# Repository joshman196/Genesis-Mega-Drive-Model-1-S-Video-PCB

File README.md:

# Sega Genesis/Mega Drive Model 1 S-Video Mod PCB
Simple PCB that carries the Luma, Chroma, and Ground lines with their respective components for a Model 1 Genesis/Mega Drive equipped with a Sony CXA1145 video encoder, enabling S-Video functionality. It is rare but still possible to instead have a Fujitsu MB3514 video encoder in a Model 1 Genesis/Mega Drive. If that is your case, then use the [Model 2 & 3 S-Video PCB instead](https://github.com/joshman196/Simple-Genesis-Model-2-and-3-S-Video-Private).

**It is recommended to use 28 AWG wire for this install.**

## Parts Needed

- 1x 220µF 6.3V Capacitor
- 1x 75 Ohm Resistor
- 1x 33 Ohm Resistor
- 1x KSC945 Transistor (If you buy this part from somewhere else, double-check that you get the KSC945 and **NOT** the KSC945**C**)

You can buy these components in a kit from [console5.com](https://console5.com/store/cxa1145-simple-s-video-mod-kit.html). Make sure to also pick up an S-Video jack as well, and conveniently enough console5 also offers these in either [socket](https://console5.com/store/mini-din-in-line-socket-4-pin-female-black-pin-type-s-video-s-vhs.html) or [panel mount](https://console5.com/store/s-video-jacks-panel-mount-black-plastic-housing-solder-type.html) configurations. The version you get depends on whether you want to drill the outer shell of your console (flush mount) or not (socket).

## Installation Steps

1. Add the components (capacitor, resistors, transistor) to the PCB and find a suitable place inside your console to put the assembled board at. You may want to put kapton tape on the area of the main board where you plan on setting the PCB at. Make sure your kapton tape layer can cover the entire bottom of the PCB. You may also choose to set it somewhere off of the main board.
2. Connect a wire from pin 15 of the CXA1145 to "C In" on the S-Video PCB.
3. Connect a wire from pin 16 of the CXA1145 to "Y In" on the S-Video PCB.
4. Connect a wire from pin 12 of the CXA1145 to "+5V In" on the S-Video PCB.
5. Connect a wire from pin 1 of the CXA1145 to "GND" on the S-Video PCB.
6. If you have heatshrink tubing that you want to use, you should prepare them on the next set of wires below before soldering the other ends of those wires. **Do not apply the heat to the tubing until after testing your install!**
7. Connect a wire from "C Out" on the S-Video PCB to the Chroma pin on the back of the S-Video jack.
8. Connect a wire from "Y Out" on the S-Video PCB to the Luma/Y pin on the back of the S-Video jack.
9. Connect a wire from "CGND" on the S-Video PCB to the Chroma-Ground pin on the back of the S-Video jack.
10. Connect a wire from "YGND" on the S-Video PCB to the Luma/Y-Ground pin on the back of the S-Video jack.
11. With the wiring all done, stick some more kapton tape from the sides over the PCB to stick it down onto the main board itself, setting the PCB on top of the other layer of kapton tape you put earlier. **DO NOT SET THE PCB DOWN ON THE BARE MAIN BOARD WITHOUT SOME KIND OF INSULATION UNDER THE S-VIDEO PCB TO PREVENT POTENTIAL SHORTS.** Electrical tape may work but that tends to leave a nasty residue, so I wouldn't recommend it.
12. You're done!

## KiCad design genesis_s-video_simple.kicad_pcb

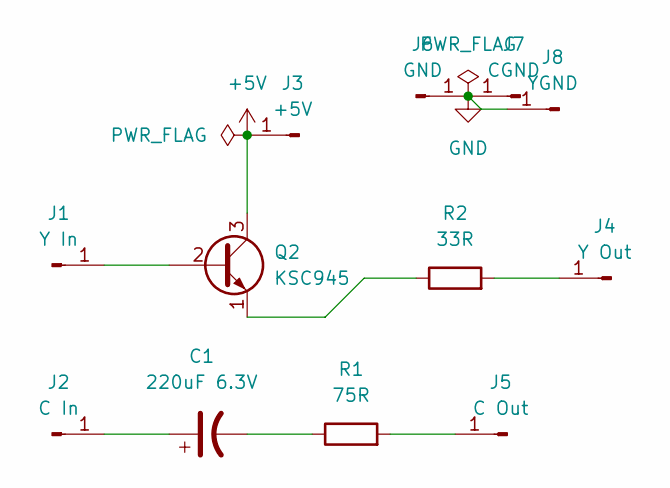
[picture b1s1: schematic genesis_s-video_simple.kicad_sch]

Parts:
C1: 220uF 6.3V; CP_Radial_D5.0mm_P2.50mm
J1: Y In; SolderWirePad_1x01_SMD_2x4mm
J2: C In; SolderWirePad_1x01_SMD_2x4mm
J3: +5V; SolderWirePad_1x01_SMD_2x4mm
J4: Y Out; SolderWirePad_1x01_SMD_2x4mm
J5: C Out; SolderWirePad_1x01_SMD_2x4mm
J6: GND; SolderWirePad_1x01_SMD_2x4mm
J7: CGND; SolderWirePad_1x01_SMD_2x4mm
J8: YGND; SolderWirePad_1x01_SMD_2x4mm
Q2: KSC945; TO-92L_Inline_Wide
R1: 75R; R_Axial_DIN0207_L6.3mm_D2.5mm_P10.16mm_Horizontal
R2: 33R; R_Axial_DIN0207_L6.3mm_D2.5mm_P10.16mm_Horizontal

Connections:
+5V: J3.1, Q2.3 (C); also elsewhere on the board
GND: J6.1, J7.1, J8.1
unnamed: C1.2, R1.1
unnamed 3: J1.1, Q2.2 (B); also elsewhere on the board
unnamed: C1.1, J2.1
unnamed: J4.1, R2.2
unnamed: J5.1, R1.2
unnamed 7: Q2.1 (E), R2.1; also elsewhere on the board

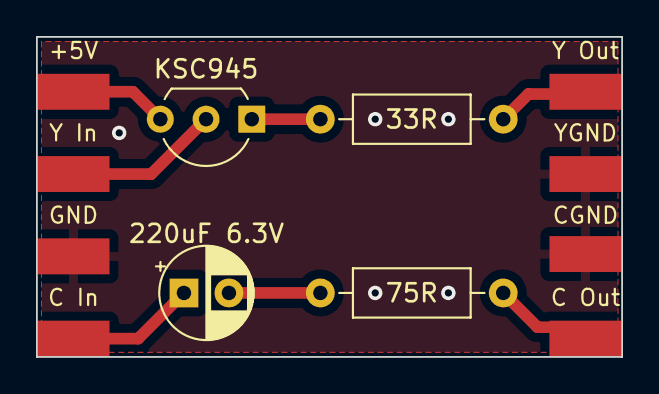
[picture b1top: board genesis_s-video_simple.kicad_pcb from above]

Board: 2 copper layers, 32.5 x 17.8 mm, 12 parts (0 on the bottom side), 8 nets.

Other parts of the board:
Q1: KSC945; TO-92L_Inline_Wide

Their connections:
+5V: Q1.3 (C); also elsewhere on the board
unnamed 3: Q1.2 (B); also elsewhere on the board
unnamed 7: Q1.1 (E); also elsewhere on the board

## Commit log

2023-08-20 initial file upload
2024-01-11 minor update
    slightly shrunk pcb, widened transistor pins for easier installation, and slight silkscreen change
